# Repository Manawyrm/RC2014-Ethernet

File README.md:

RC2014 RTL8019 Ethernet card
---------------------

The design is optimized for automated assembly at [JLCPCB](https://jlcpcb.com/DDE).  

[Schematic](gerbers/RevA/RevA.pdf)  
[Firmware](https://github.com/Manawyrm/RC2014-Ethernet-Firmware)  

Rev. A Errata:   
- Reset polarity is wrong, reset trace needs to be cut and wired to VCC (reset is done in software)
- Interrupt polarity is also wrong, remove R7. (to use interrupts, use an N-channel MOSFET to drive the INT line. Untested!)
- RTL8019 requires an SPI 9346 EEPROM for it's configuration data (for full-duplex ethernet, correct function of the LEDs, proper MAC addresses), which is missing
- RTL8019 footprint is wrong (too small). JLCPCB can still assemble these boards, but it's marked as a manufacturing error.

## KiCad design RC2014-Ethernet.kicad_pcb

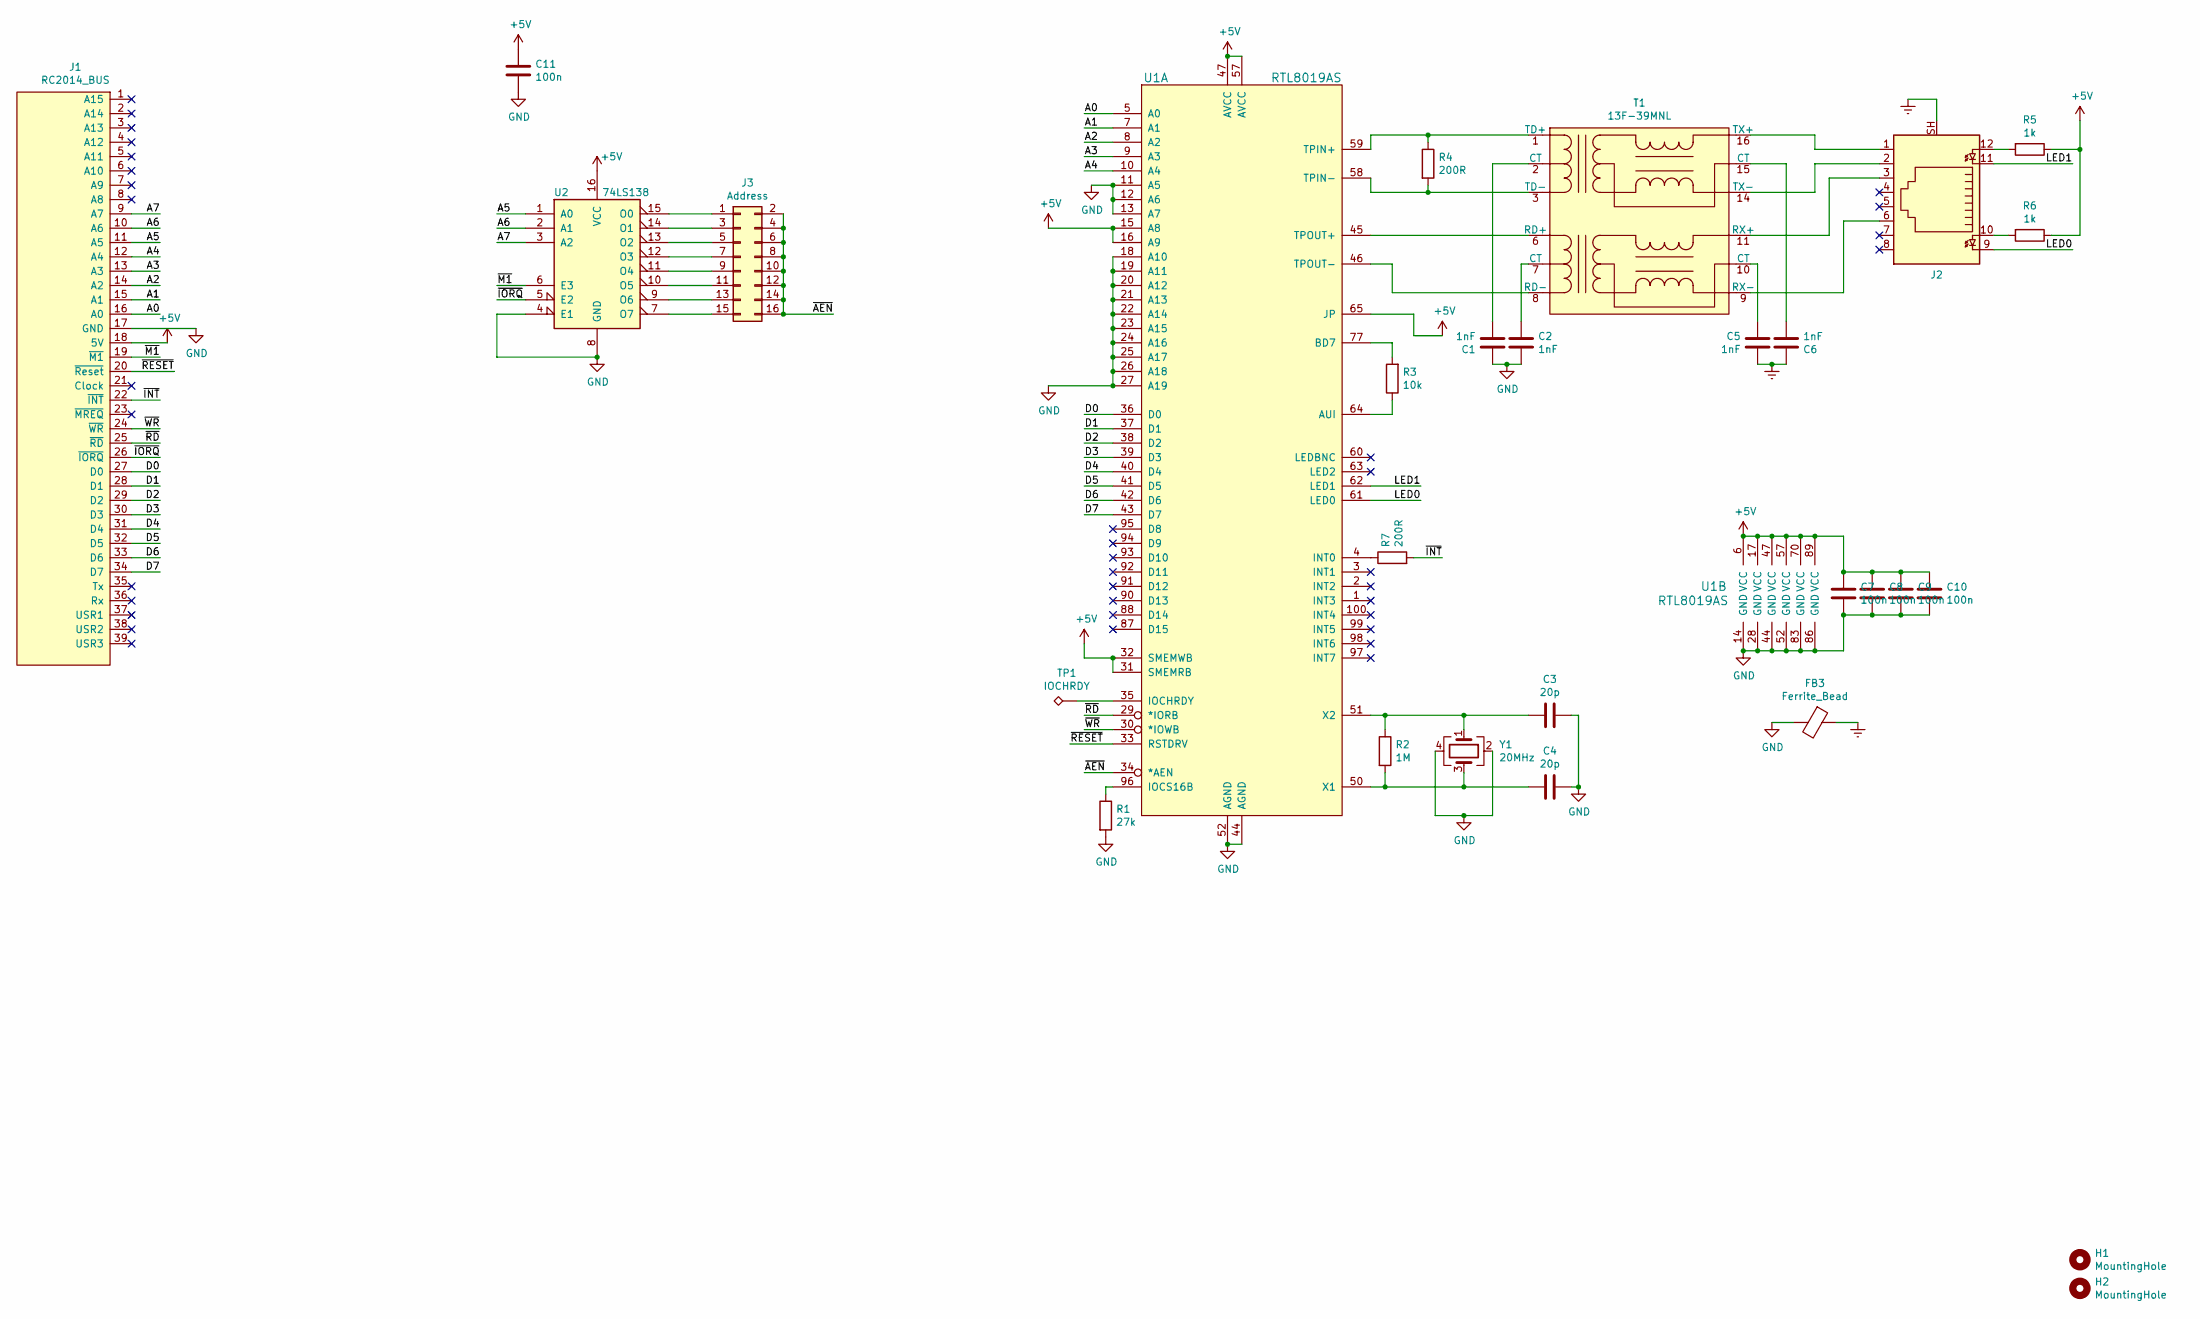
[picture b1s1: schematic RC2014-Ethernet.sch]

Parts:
C1, C2, C5, C6: 1nF; C_1206_3216Metric; LCSC C9196
C3, C4: 20p; C_0402_1005Metric; LCSC C1554
C7, C8, C9, C10, C11: 100n; C_0402_1005Metric; LCSC C1525
FB3: Ferrite_Bead; L_0805_2012Metric; LCSC C1017
H1, H2: MountingHole; ToolingHole_JLCSMT
J1: RC2014_BUS; PinHeader_1x39_P2.54mm_Vertical
J2: 8P8C_Shielded; 8P8C_yellow_green_Ckmtw_C133529
J3: Address; PinHeader_2x08_P2.54mm_Vertical
R1: 27k; R_0402_1005Metric; LCSC C25771
R2: 1M; R_0402_1005Metric; LCSC C26083
R3: 10k; R_0402_1005Metric; LCSC C25744
R4, R7: 200R; R_0402_1005Metric; LCSC C25087
R5, R6: 1k; R_0402_1005Metric; LCSC C11702
T1: 13F-39MNL; SOIC-16W-12_7.5x10.3mm_P1.27mm; LCSC C115949
TP1: IOCHRDY; TestPoint_Pad_2.5x2.5mm
U1: RTL8019AS; PQFP-100_14x20mm_P0.65mm; LCSC C10016
U2: 74LS138; SOIC-16_3.9x9.9mm_P1.27mm; LCSC C5602
Y1: 20MHz; Crystal_SMD_3225-4Pin_3.2x2.5mm; LCSC C110936

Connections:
+5V: C7.1, C8.1, C9.1, C10.1, C11.1, J1.18 (5V), R5.1, R6.1, U1.6 (VCC), U1.15 (A8), U1.16 (A9), U1.17 (VCC), U1.31 (SMEMRB), U1.32 (SMEMWB), U1.47 (AVCC), U1.57 (AVCC), U1.65 (JP), U1.70 (VCC), U1.89 (VCC), U2.16 (VCC)
/A0: J1.16 (A0), U1.5 (A0)
/A1: J1.15 (A1), U1.7 (A1)
/A2: J1.14 (A2), U1.8 (A2)
/A3: J1.13 (A3), U1.9 (A3)
/A4: J1.12 (A4), U1.10 (A4)
/A5: J1.11 (A5), U2.1 (A0)
/A6: J1.10 (A6), U2.2 (A1)
/A7: J1.9 (A7), U2.3 (A2)
/D0: J1.27 (D0), U1.36 (D0)
/D1: J1.28 (D1), U1.37 (D1)
/D2: J1.29 (D2), U1.38 (D2)
/D3: J1.30 (D3), U1.39 (D3)
/D4: J1.31 (D4), U1.40 (D4)
/D5: J1.32 (D5), U1.41 (D5)
/D6: J1.33 (D6), U1.42 (D6)
/D7: J1.34 (D7), U1.43 (D7)
/LED0: J2.9, U1.61 (LED0)
/LED1: J2.11, U1.62 (LED1)
/~AEN: J3.2, J3.4, J3.6, J3.8, J3.10, J3.12, J3.14, J3.16, U1.34 (*AEN)
/~INT: J1.22 (~INT), R7.2
/~IORQ: J1.26 (~IORQ), U2.5 (E2)
/~M1: J1.19 (~M1), U2.6 (E3)
/~RD: J1.25 (~RD), U1.29 (*IORB)
/~RESET: J1.20 (~Reset), U1.33 (RSTDRV)
/~WR: J1.24 (~WR), U1.30 (*IOWB)
Earth: C5.2, C6.1, FB3.1, J2.SH
GND: C1.1, C2.2, C3.1, C4.1, C7.2, C8.2, C9.2, C10.2, C11.2, FB3.2, J1.17 (GND), R1.2, U1.11 (A5), U1.12 (A6), U1.13 (A7), U1.14 (GND), U1.18 (A10), U1.19 (A11), U1.20 (A12), U1.21 (A13), U1.22 (A14), U1.23 (A15), U1.24 (A16), U1.25 (A17), U1.26 (A18), U1.27 (A19), U1.28 (GND), U1.44 (AGND), U1.52 (AGND), U1.83 (GND), U1.86 (GND), U2.4 (E1), U2.8 (GND), Y1.2, Y1.4
unnamed: C1.2, T1.2 (CT)
unnamed: C2.1, T1.7 (CT)
unnamed: C3.2, R2.1, U1.51 (X2), Y1.1
unnamed: C4.2, R2.2, U1.50 (X1), Y1.3
unnamed: C5.1, T1.10 (CT)
unnamed: C6.2, T1.15 (CT)
unnamed: J2.1, T1.16 (TX+)
unnamed: J2.2, T1.14 (TX-)
unnamed: J2.3, T1.11 (RX+)
unnamed: J2.6, T1.9 (RX-)
unnamed: J2.10, R6.2
unnamed: J2.12, R5.2
unnamed: J3.1, U2.15 (O0)
unnamed: J3.3, U2.14 (O1)
unnamed: J3.5, U2.13 (O2)
unnamed: J3.7, U2.12 (O3)
unnamed: J3.9, U2.11 (O4)
unnamed: J3.11, U2.10 (O5)
unnamed: J3.13, U2.9 (O6)
unnamed: J3.15, U2.7 (O7)
unnamed: R1.1, U1.96 (IOCS16B)
unnamed: R3.1, U1.64 (AUI)
unnamed: R3.2, U1.77 (BD7)
unnamed: R4.1, T1.1 (TD+), U1.59 (TPIN+)
unnamed: R4.2, T1.3 (TD-), U1.58 (TPIN-)
unnamed: R7.1, U1.4 (INT0)
unnamed: T1.6 (RD+), U1.45 (TPOUT+)
unnamed: T1.8 (RD-), U1.46 (TPOUT-)
unnamed: TP1.1, U1.35 (IOCHRDY)

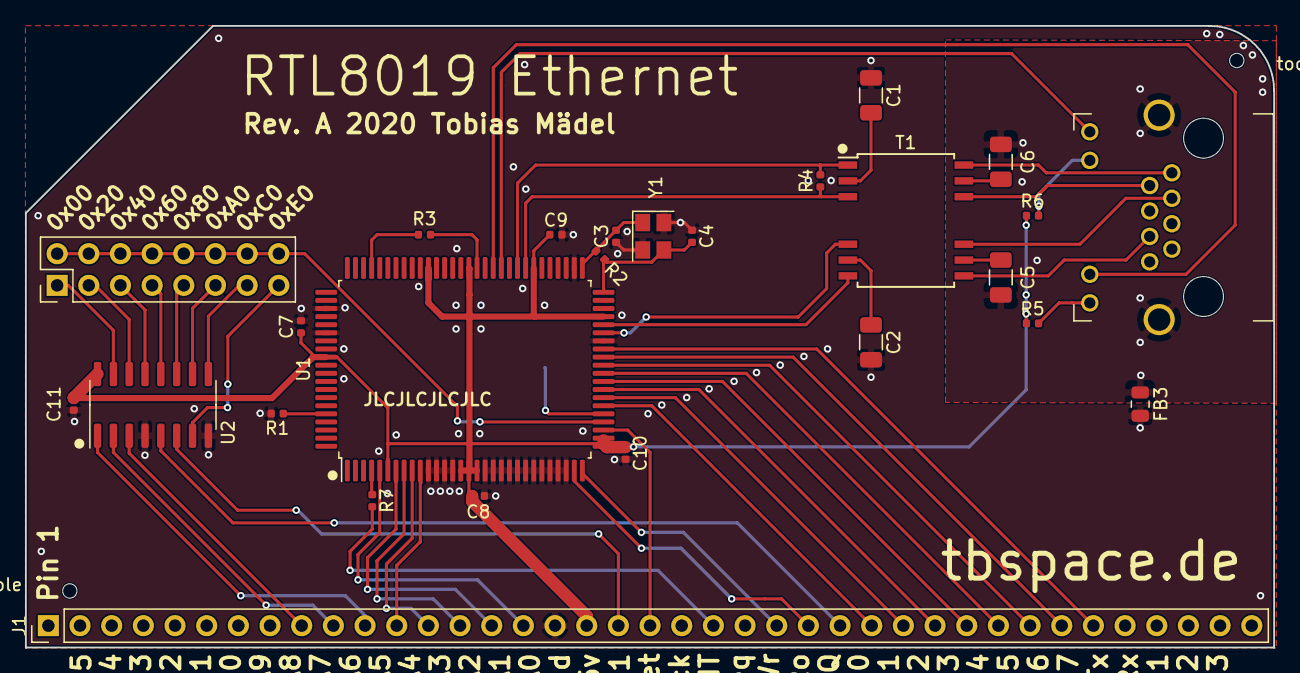
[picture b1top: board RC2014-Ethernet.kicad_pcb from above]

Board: 2 copper layers, 100.1 x 49.9 mm, 29 parts (1 on the bottom side), 57 nets.

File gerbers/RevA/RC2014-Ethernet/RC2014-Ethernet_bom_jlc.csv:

"Comment","Designator","Footprint","LCSC Part #"
"1nF","C2,C1,C5,C6","C_1206_3216Metric","C9196"
"20p","C3,C4","C_0402_1005Metric","C1554"
"100n","C7,C9,C10,C8,C11","C_0402_1005Metric","C1525"
"Ferrite_Bead","FB3","L_0805_2012Metric","C1017"
"27k","R1","R_0402_1005Metric","C25771"
"1M","R2","R_0402_1005Metric","C26083"
"10k","R3","R_0402_1005Metric","C25744"
"200R","R4,R7","R_0402_1005Metric","C25087"
"1k","R5,R6","R_0402_1005Metric","C11702"
"13F-39MNL","T1","SOIC-16W-12_7.5x10.3mm_P1.27mm","C115949"
"RTL8019AS","U1","PQFP-100_14x20mm_P0.65mm","C10016"
"74LS138","U2","SOIC-16_3.9x9.9mm_P1.27mm","C5602"
"20MHz","Y1","Crystal_SMD_3225-4Pin_3.2x2.5mm","C110936"

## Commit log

2020-08-10 Schematic, address layout, modified symbol
2020-08-16 add address decoding and first traces
2020-08-16 Finish layout
2020-08-26 RevA, Tooling holes, via stitching
2020-08-30 Add readme and schematic pdf
